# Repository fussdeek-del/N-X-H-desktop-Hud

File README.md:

# N X H — The Desktop HUD

> A always-on hardware HUD that sits on ur desk and shows live CPU, RAM, DISK, FPS and TIME — no alt-tabbing, no task manager, just plug and go.

---

## What is it?

NXH is a compact always-on HUD built around the Raspberry Pi Pico. It plugs into any PC via USB-C and shows live system stats CPU usage, RAM, disk, FPS, and time on a 2.4" ST7789V TFT display (240×320, SPI). The whole thing sits in a custom 3D-printed enclosure I designed in FreeCAD. No software window to manage, no hotkeys, it is just always there on ur desk showing you what ur PC is doing.

## Why I built it

My PC isn't that powerful tbh. Whenever I push it on gaming, rendering, compiling I always needed to know if it's hitting the limit. Opening task manager takes too long and gets in the way. I wanted something that just *sits there* and tells me. So I built it. Hack Club gave me the chance to actually do it for real, with a proper coustum PCBs and everything. Huge shout out to them 🙌

---

## Demo

---

## Features

- Raspberry Pi Pico (RP2040) as the main MCU
- 2.4" ST7789V TFT display  240×320, SPI, 3.3V
- USB-C connectivity (power + data, no drivers needed)
- Custom 2-layer PCB designed from scratch in KiCad
- 3D-printed enclosure designed in FreeCAD back lid, front panel, internal mounts
- C++ firmware running on the Pico
- Lightweight companion desktop app (Python) select which stats to display
- Hardware reset button (SW1) wired to RUN pin
- Onboard decoupling capacitors on the 3.3V rail (100nF + 10µF)
- Displays: CPU %, RAM %, Disk %, FPS, System Time

---

## Hardware

| Component | Spec | Qty | Price | Link |
|---|---|---|---|---|
| Raspberry Pi Pico | RP2040, 2MB flash — must be original with TP1/TP2/TP3 test pads | ×1 | $3.53 | [Buy](https://www.aliexpress.com/item/1005008948799927.html) |
| 2.4" TFT Display | ST7789V driver, 240×320, SPI, 8-pin, 3.3V | ×1 | $4.47 | [Buy](https://www.aliexpress.com/item/1005009546154656.html) |
| USB-C Connector | Female SMD 16-pin, horizontal mount, USB 2.0 — GCT USB4105-GF-A footprint | ×1 (pack of 5) | $1.17 | [Buy](https://www.aliexpress.com/item/1005008515699009.html) |
| Resistor 5.1kΩ 0805 | R1, R2 — CC1/CC2 USB-C pull-downs | ×2 (pack of 100) | $1.72 | [Buy](https://www.aliexpress.com/item/1005009613956367.html) |
| Resistor 27Ω 0805 | R4, R5 — USB D+/D− series resistors | ×2 (pack of 100) | $0.46 | [Buy](https://www.aliexpress.com/item/32997835881.html) |
| Resistor 0Ω 0805 | R3 — AGND to GND bridge jumper | ×1 (pack of 100) | $0.71 | [Buy](https://www.aliexpress.com/item/1005007446894308.html) |
| Capacitor 100nF 0805 | C1 — 3.3V rail decoupling, 50V X7R ceramic | ×1 (pack of 100) | $6.11 | [Buy](https://www.aliexpress.com/item/1005012084340996.html) |
| Capacitor 10µF 0805 | C2 — 3.3V rail bulk cap, 10V X5R ceramic | ×1 (pack of 50) | $2.30 | [Buy](https://www.aliexpress.com/item/32911735940.html) |
| Tactile Push Button | 6×6mm SMD 4-pin, 4.3mm height — SW1 reset | ×1 (pack of 20) | $1.95 | [Buy](https://www.aliexpress.com/item/1005006870418414.html) |
| Male Pin Header 2.54mm | Single row 40-pin (snap to 8) — J1 TFT connector | ×1 | $0.90 | [Buy](https://www.aliexpress.com/item/32670970932.html) |
| PCB Manufacturing | 2-layer, FR-4, 1.6mm, HASL — upload Gerber to JLCPCB | ×5 boards | $3.00 | [JLCPCB](https://jlcpcb.com) |
| 3D Enclosure | Custom HUD case — upload STL to JLC3DP | ×1 | $16.78 | [JLC3DP](https://jlc3dp.com) |
| M2 × 6mm Screw + Nut | Stainless steel — 4 sets mount PCB and Pico to case posts | ×4 sets (kit of 50) | $0.30 | [Buy](https://www.aliexpress.com/item/1005003157957734.html) |
| M3 × 10mm Screw + Nut | Stainless steel — 4 sets close the back lid | ×4 sets (kit of 50) | $0.30 | [Buy](https://www.aliexpress.com/item/1005003157957734.html) |
| USB-A to USB-C Cable | 1m, data + power capable (not charge-only) | ×1 | $1.90 | [Buy](https://www.aliexpress.com/item/1005006121990031.html) |
| USB-C Extension Cable | USB-C 3.1 Gen2, PD 100W, 5A — optional if ur port is hard to reach | ×1 | $2.42 | [Buy](https://www.aliexpress.com/item/1005006904002741.html) |

[`BOM components.csv`](BOM%20components.csv)

---

## How to use

## Build & Installation Guide

### Parts needed
See full BOM table above with links.

### PCB Assembly
1. Order PCB using gerbers.zip from JLCPCB
2. Solder SMD components first: R1, R2 (5.1k), R3 (0Ω), R4, R5 (27Ω), C1 (100nF), C2 (10uF), SW1
3. Solder USB-C connector J2
4. Place Raspberry Pi Pico on pin headers
5. Connect TFT display to J1 connector

### Flash Firmware
1. Hold BOOTSEL on Pico and plug USB-C
2. Copy FIRMWARE/hud-firmware/SRC/main.cpp compiled .uf2 to the drive
3. Pico reboots automatically

### Run the companion app

1. Make sure Python is installed — if not, [download it here](https://python.org)
2. Install dependencies:
   ```
   pip install -r app/requirements.txt
   ```
3. Run the app:
   ```
   python app/main.py
   ```
4. The HUD Monitor window opens — tick which stats you want shown on the display (CPU, RAM, DISK, TIME, FPS)
5. The device updates in real time as long as it's connected

> The app talks to the Pico over serial (USB). If it says "no pico" in the top right, unplug and replug the USB-C cable.

---

## Repo structure

```
NXH/
├── README.md
├── BOM components.csv
│
├── APP/
│   └── hud-app/
│       ├── main.py
│       ├── config.py
│       ├── metrics.py
│       ├── tray.py
│       ├── hud_settings.json
│       └── core/
│           ├── formatter.py
│           ├── metrics.py
│           ├── sender.py
│           └── __init__.py
│
├── ASSETS/
│   ├── banner.png
│   ├── exploded.png
│   ├── front.png
│   ├── pcb.png
│   ├── schematic.png
│   ├── app-screenshot.png
│   ├── wiring.png
│   └── zine-page.png
│
├── CAD/
│   ├── HUD case neww.FCStd          ← FreeCAD source
│   ├── HUD case new.step            ← full assembly export
│   ├── PCB new.step                 ← PCB 3D model
│   └── Display TFT-ST7789-240X320 V2.step
│
├── FIRMWARE/
│   └── hud-firmware/
│       ├── platformio.ini
│       └── SRC/
│           └── main.cpp
│
└── PCB/
    ├── gerber new.zip               ← submit this to JLCPCB
    └── PCB new/
        ├── real PCB.kicad_pro
        ├── real PCB.kicad_sch
        └── real PCB.kicad_pcb
```
---

## Wiring diagram

| Pico pin | TFT pin | Signal |
|---|---|---|
| GP17 | CS | Chip select |
| GP18 | SCK | SPI clock |
| GP19 | MOSI | SPI data |
| GP20 | DC | Data/command |
| GP21 | RST | Reset |
| GP22 | BL | Backlight |
| 3V3 (pin 36) | VCC | 3.3V power |
| GND (pin 38) | GND | Ground |

---

## Zine page

*Made for Hack Club Fallout -- Shenzhen 2025*

---

## Credits

- [KiCad](https://www.kicad.org/) — PCB design and schematic
- [FreeCAD](https://www.freecad.org/) — 3D enclosure design
- [Hack Club Fallout](https://fallout.hackclub.com) — grant program that made this real
- Python + psutil — companion app backend

Made with love by **Nabeel (18) × Hashir (17)** — Pakistan 🇵🇰

---

## License

This project is licensed under the [MIT License](LICENSE).

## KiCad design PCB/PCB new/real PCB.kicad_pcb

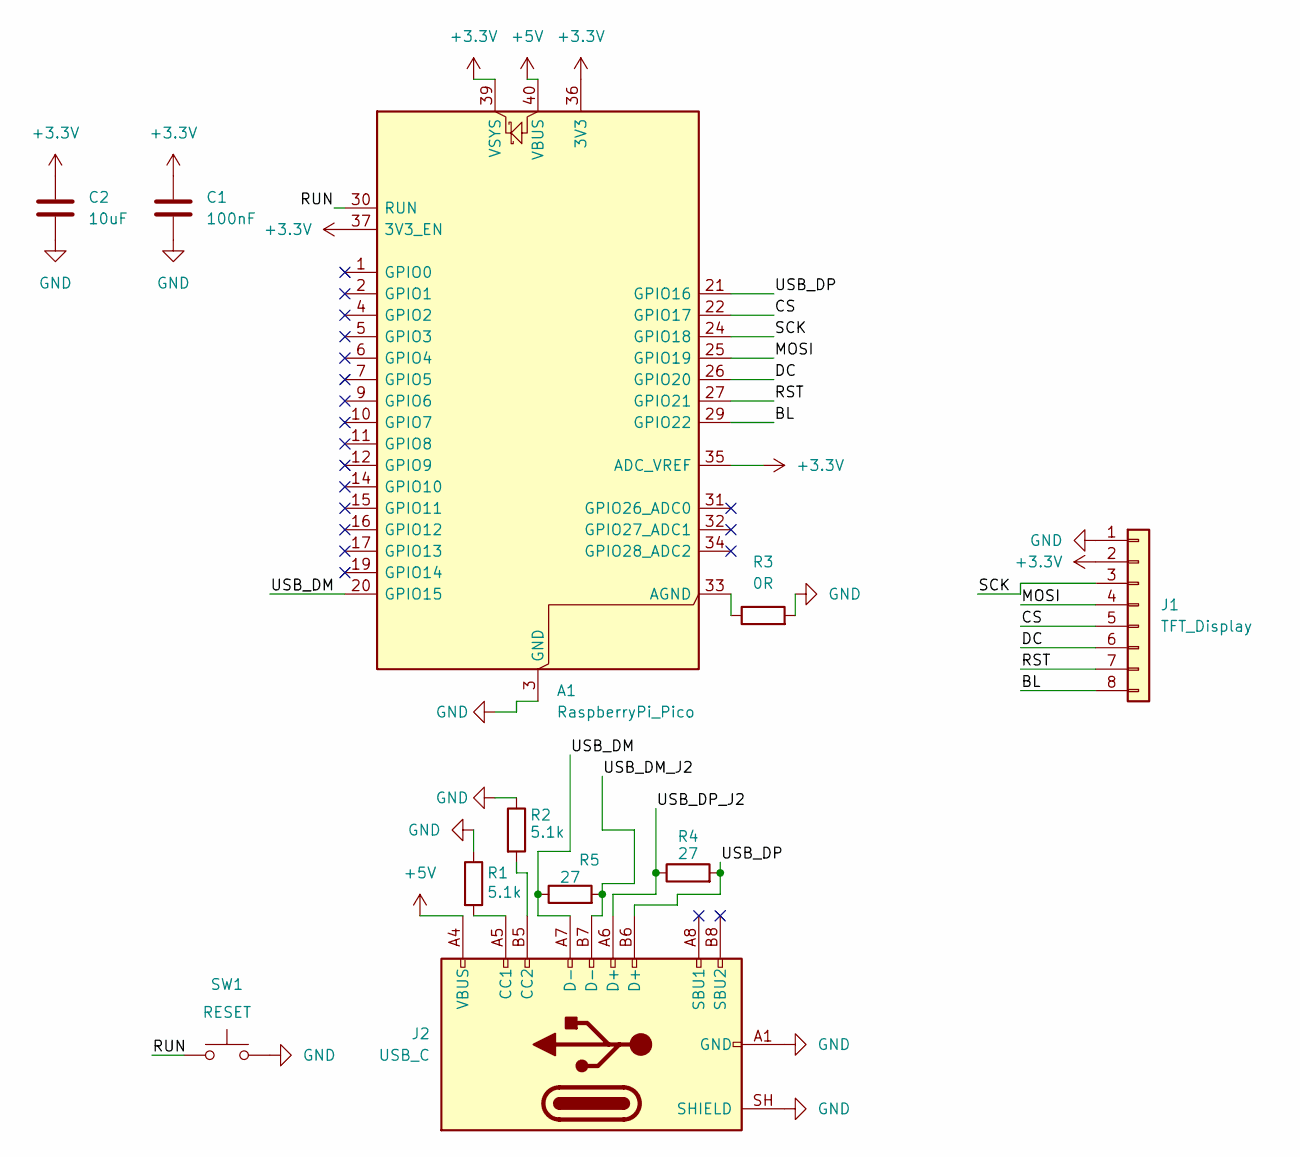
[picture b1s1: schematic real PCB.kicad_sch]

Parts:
A1: RaspberryPi_Pico; RaspberryPi_Pico_Common_Unspecified
C1: 100nF; C_0805_2012Metric
C2: 10uF; C_0805_2012Metric
J1: TFT_Display; PinHeader_1x08_P2.54mm_Vertical
J2: USB_C; USB_C_Receptacle_GCT_USB4105-xx-A_16P_TopMnt_Horizontal
R1, R2: 5.1k; R_0805_2012Metric
R3: 0R; R_0805_2012Metric
R4, R5: 27; R_0805_2012Metric
SW1: RESET; SW_Push_1TS009xxxx-xxxx-xxxx_6x6x5mm

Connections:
+3.3V: A1.35 (ADC_VREF), A1.36 (3V3), A1.37 (3V3_EN), A1.39 (VSYS), C1.1, C2.1, J1.2
+5V: A1.40 (VBUS), J2.A4 (VBUS), J2.A9 (VBUS), J2.B4 (VBUS), J2.B9 (VBUS)
/BL: A1.29 (GPIO22), J1.8
/CS: A1.22 (GPIO17), J1.5
/DC: A1.26 (GPIO20), J1.6
/MOSI: A1.25 (GPIO19), J1.4
/RST: A1.27 (GPIO21), J1.7
/RUN: A1.30 (RUN), SW1.1
/SCK: A1.24 (GPIO18), J1.3
/USB_DM: A1.20 (GPIO15), J2.A7 (D-), R5.1
/USB_DM_J2: J2.B7 (D-), R5.2
/USB_DP: A1.21 (GPIO16), J2.B6 (D+), R4.2
/USB_DP_J2: J2.A6 (D+), R4.1
GND: A1.3 (GND), A1.8 (GND), A1.13 (GND), A1.18 (GND), A1.23 (GND), A1.28 (GND), A1.38 (GND), C1.2, C2.2, J1.1, J2.A1 (GND), J2.A12 (GND), J2.B1 (GND), J2.B12 (GND), J2.SH (SHIELD), R1.1, R2.1, R3.2, SW1.2
unnamed: A1.33 (AGND), R3.1
unnamed: J2.A5 (CC1), R1.2
unnamed: J2.B5 (CC2), R2.2

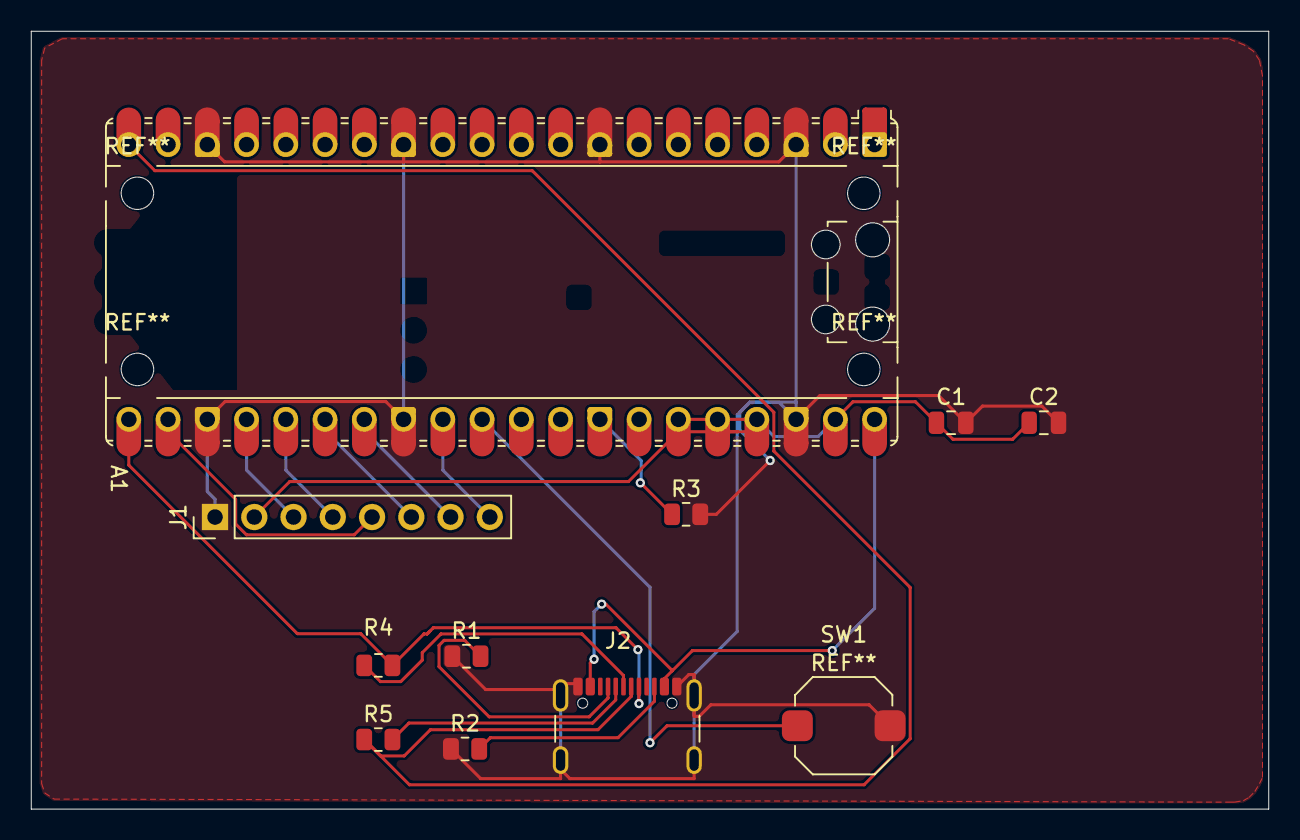
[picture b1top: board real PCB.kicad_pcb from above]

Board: 2 copper layers, 80.1 x 50.3 mm, 11 parts (0 on the bottom side), 17 nets.

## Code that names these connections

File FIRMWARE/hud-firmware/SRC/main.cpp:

// hUD Firmware for RP2040 + ST7789
// reads serial data from PC and displays on TFT

#include <Arduino.h>
#include <Adafruit_GFX.h>
#include <Adafruit_ST7789.h>
#include <SPI.h>

// PIN CONFIG (matched to your PCB schematic) 
#define TFT_CS    17   // GPIO17 - pin 22 on Pico
#define TFT_DC    20   // GPIO20 - pin 26 on Pico
#define TFT_RST   21   // GPIO21 - pin 27 on Pico
#define TFT_BL    22   // GPIO22 - pin 29 on Pico (backlight)

Adafruit_ST7789 tft = Adafruit_ST7789(TFT_CS, TFT_DC, TFT_RST);

//  DATA VARIABLES 
String fps     = "--";
String cpu     = "--";
String ram     = "--";
String disk    = "--";
String timeStr = "--:--:--";

// Keep previous values to avoid redrawing unchanged fields
String prev_fps     = "";
String prev_cpu     = "";
String prev_ram     = "";
String prev_disk    = "";
String prev_time    = "";

// COLORS 
#define COLOR_BG     0x0000   // Black background
#define COLOR_LABEL  0x4A49   // Muted grey for labels
#define COLOR_VALUE  0xFFFF   // White for values
#define COLOR_BOX    0x2124   // Dark box behind each row

//  DRAW ONE ROW (no-flicker: only redraws value if changed) 
void drawRow(int y, const char* label, String value, String& prev, const char* unit = "") {
  if (value == prev) return;  // skip if nothing changed

  // Erase old value area only (not the whole screen)
  tft.fillRect(100, y, 140, 24, COLOR_BG);

  // Draw value
  tft.setTextColor(COLOR_VALUE);
  tft.setTextSize(2);
  tft.setCursor(100, y);
  tft.print(value);
  if (strlen(unit) > 0) tft.print(unit);

  prev = value;
}

//  DRAW STATIC LABELS (called once at startup)
void drawLabels() {
  tft.setTextColor(COLOR_LABEL);
  tft.setTextSize(2);

  tft.setCursor(10, 20);  tft.print("FPS :");
  tft.setCursor(10, 60);  tft.print("CPU :");
  tft.setCursor(10, 100); tft.print("RAM :");
  tft.setCursor(10, 140); tft.print("DSK :");
  tft.setCursor(10, 190); tft.print("TIME:");
}

//  PARSE INCOMING SERIAL LINE 
void parseData(String data) {
  int start;

  start = data.indexOf("FPS:");
  if (start != -1) fps = data.substring(start + 4, data.indexOf(';', start));

  start = data.indexOf("CPU:");
  if (start != -1) cpu = data.substring(start + 4, data.indexOf(';', start));

  start = data.indexOf("RAM:");
  if (start != -1) ram = data.substring(start + 4, data.indexOf(';', start));

  start = data.indexOf("DISK:");
  if (start != -1) disk = data.substring(start + 5, data.indexOf(';', start));

  start = data.indexOf("TIME:");
  if (start != -1) timeStr = data.substring(start + 5, data.indexOf(';', start));
}

//  SETUP 
void setup() {
  Serial.begin(115200);

  // Turn on backlight
  pinMode(TFT_BL, OUTPUT);
  digitalWrite(TFT_BL, HIGH);

  // Init display
  tft.init(240, 240);
  tft.setRotation(0);
  tft.fillScreen(COLOR_BG);

  // Draw static labels once
  drawLabels();
}

//  LOOP 
void loop() {
  if (Serial.available()) {
    String data = Serial.readStringUntil('\n');
    parseData(data);

    // only redraws rows where value actually changed — no flicke
    drawRow(20,  "FPS :", fps,     prev_fps);
    drawRow(60,  "CPU :", cpu,     prev_cpu,  "%");
    drawRow(100, "RAM :", ram,     prev_ram,  "%");
    drawRow(140, "DSK :", disk,    prev_disk, "%");
    drawRow(190, "TIME:", timeStr, prev_time);
  }
}

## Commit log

2026-04-19 Revise README for N X H Desktop HUD
    Expanded README with project details, features, usage instructions, and credits.
2026-04-19 Revise README for better readability and details
    Updated README.md for clarity and improved formatting.
2026-04-19 Revise project structure in README
    Updated project structure and added new directories for BOM, APP, ASSETS, CAD, FIRMWARE, and PCB.
2026-04-19 Update README with wiring diagram and zine page
    Added wiring diagram and zine page sections to README.
2026-04-19 Remove sections from README.md
    Removed wiring diagram, zine page, credits, and license sections from the README.
2026-04-19 Update README with wiring diagram and credits
    Added wiring diagram and zine page sections to README.
2026-04-19 Fix formatting issues in README.md
2026-04-19 Update image paths in README.md to uppercase
2026-04-19 initial project upload
    initial project upload
2026-04-19 banner added
2026-04-19 Remove banner image from README
    Removed banner image from README.
2026-04-19 Refactor README for clarity and readability
    Removed unnecessary punctuation and improved readability in the README.
2026-04-20 Fix formatting in README description
    Removed unnecessary hyphen before 'on a 2.4" ST7789V TFT display'.
2026-04-20 Update BOM file link in README
2026-04-20 Fix link to BOM components in README.md
2026-04-20 Update pin assignments for TFT display in README
2026-04-20 Add MIT License to the project
2026-04-20 Fix link formatting for BOM components in README
2026-04-20 Revise README with installation and assembly details
    Updated the README to include a build and installation guide, parts needed, and PCB assembly instructions.
2026-04-20 del pychece
2026-04-20 name changing
2026-04-20 Clean up wiring diagram section in README
    Removed HTML tags around the wiring diagram image.
2026-04-20 update bom prices
2026-04-23 minor changes
2026-04-24 Fix spelling error in README
    Corrected spelling of 'custom' in the README.
2026-04-26 Fix typo in Zine page description

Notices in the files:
README.md:
License: MIT
